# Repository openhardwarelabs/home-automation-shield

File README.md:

home-automation-shield
======================

Home Automation shield for Arduino

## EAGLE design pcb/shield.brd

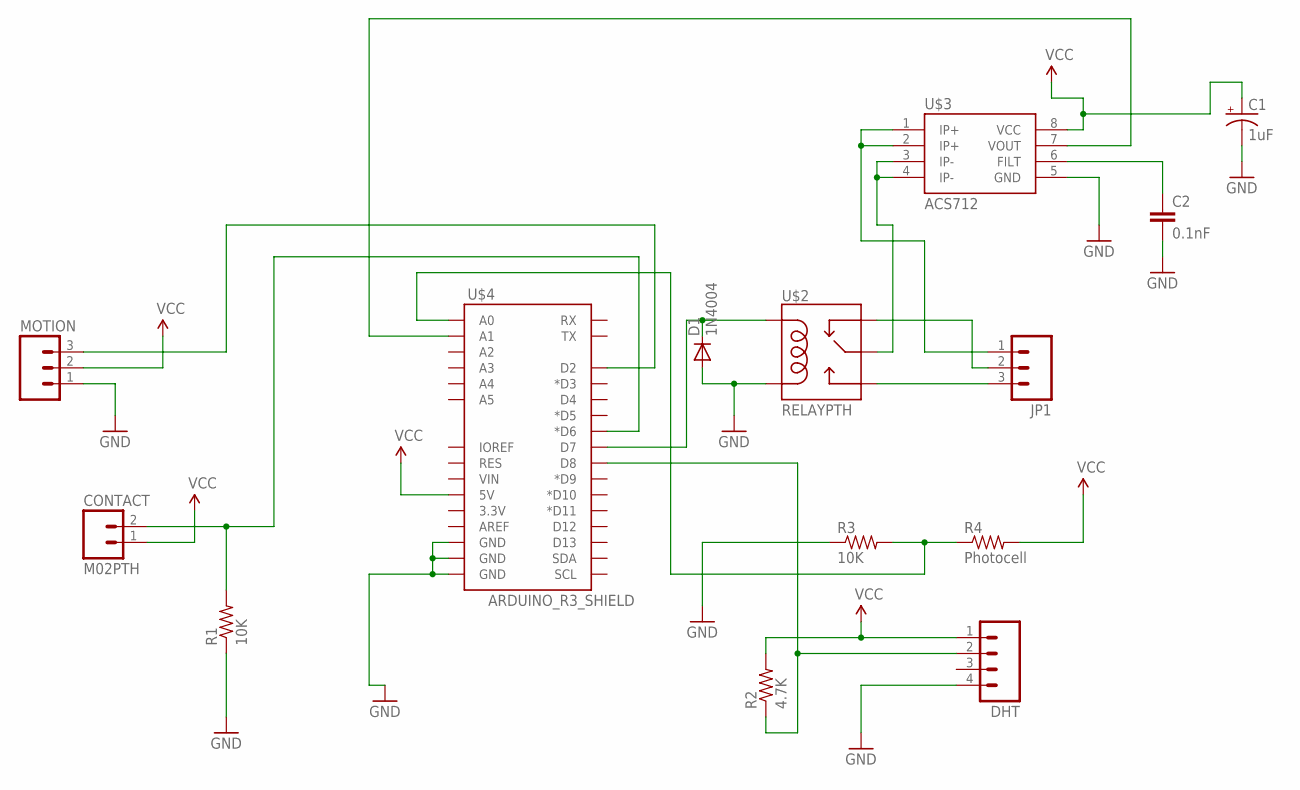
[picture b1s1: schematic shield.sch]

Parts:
C1: 1uF; CPOL-RADIAL-10UF-25V
C2: 0.1nF; CAP-PTH-SMALL2
CONTACT: M02PTH; 1X02
D1: 1N4004; DO41-10
DHT: M04LOCK; 1X04_LOCK
JP1: M03SCREW; SCREWTERMINAL-3.5MM-3
MOTION: M03PTH; 1X03
R1, R3: 10K; AXIAL-0.3
R2: 4.7K; AXIAL-0.3
R4: Photocell; AXIAL-0.3
U$2: RELAYPTH; RELAY-G5Q
U$3: ACS712; SO08
U$4: ARDUINO_R3_SHIELD; UNO_R3_SHIELD

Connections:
GND: C1.2 (-), C2.2, D1.A, DHT.4, MOTION.1, R1.P$1 (1), R3.P$1 (1), U$2.1 (COIL2), U$3.5 (GND), U$4.GND@0 (GND), U$4.GND@1 (GND), U$4.GND@2 (GND)
unnamed: R3.P$2 (2), R4.P$1 (1), U$4.A0
unnamed: D1.C, U$2.5 (COIL1), U$4.D7
unnamed: JP1.2, U$2.4 (NC)
unnamed: U$2.2 (MAIN), U$3.3 (IP-), U$3.4 (IP-)
unnamed: JP1.3, U$2.3 (NO)
unnamed: JP1.1, U$3.1 (IP+), U$3.2 (IP+)
unnamed: C2.1, U$3.6 (FILT)
unnamed: MOTION.3, U$4.D2
unnamed: DHT.2, R2.P$1 (1), U$4.D8
unnamed: CONTACT.2, R1.P$2 (2), U$4.D6 (*D6)
unnamed: U$3.7 (VOUT), U$4.A1
VCC: C1.1 (+), CONTACT.1, DHT.1, MOTION.2, R2.P$2 (2), R4.P$2 (2), U$3.8 (VCC), U$4.5V

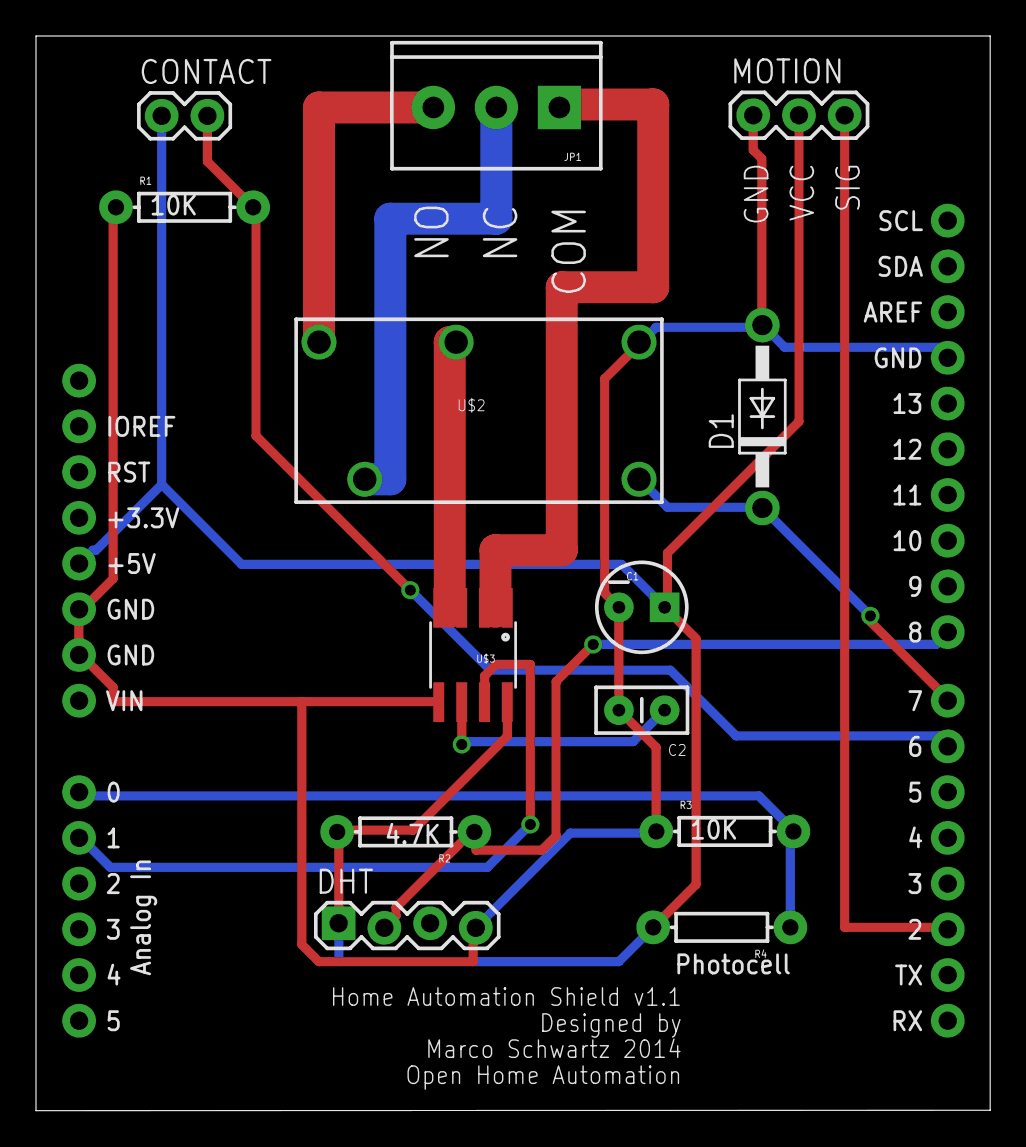
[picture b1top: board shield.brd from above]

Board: 2 copper layers, 53.0 x 59.7 mm, 14 parts (0 on the bottom side), 13 nets.

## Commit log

2014-09-04 initial commit cleanup

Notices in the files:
parts and their libraries:
SparkFun-Boards: Licensing: CC v3.0 Share-Alike You are welcome to use this library for commercial purposes.
SparkFun-AnalogIC: Licensing:Creative Commons ShareAlike 4.0 International - https://creativecommons.org/licenses/by-sa/4.0
